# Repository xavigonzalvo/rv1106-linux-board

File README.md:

# RV1106G3 Linux board (Rev A)

An 80 × 80 mm Linux board around the Rockchip RV1106G3 (Cortex-A7, 256 MB DDR3L in package, 1 TOPS NPU), with
SPI NAND, microSD, 100 Mb Ethernet, USB-C (power + OTG), USB-A host and a 2×20 header.
Board #1 boots Linux, is on the network, runs YOLOv5 on the NPU (2026-11-20) and a 135M-parameter chat model on
the CPU (2026-11-21).

First bring-up (2026-11-20, details in `design/LOG.md` and `software/BOARD-QUICKSTART.md`): the blank board
appeared on the Mac as a Rockchip device in recovery mode, then booted Linux from its own flash and got on the
network.

| Recovery mode over USB-C | Linux on Ethernet |
|---|---|
|  |  |

| Folder | What |
|---|---|
| `PLAN.md` | the project plan and phases |
| `design/` | requirements, decisions (`decisions.md`), schematic, PCB (`pcb/`, fab files in `pcb/fab/`), bring-up procedure and log (`bringup.md`, `LOG.md`), datasheets and references (`refs/`) |
| `software/` | board support for the Luckfox SDK, flashing tools, Docker cross-compiler, examples |
| `software/BOARD-QUICKSTART.md` | **start here** to flash and use a board |
| `software/examples/ai-detect/` | object detection on the NPU with a web UI |
| `software/examples/tiny-llm/` | SmolLM2-135M-Instruct chat on the CPU (`chat` in the board shell) |
| `dashboard/` | project status page |
| `case/` | 3D-printable enclosure (OpenSCAD source + STLs, with and without the V-cut rails) |
| `release/rev-a/` | **ordering bundle**: JLCPCB upload zip, BOM, CPL, order notes, case STLs, device trees; rebuilt by `release/make_release.sh` |

## Not in this repo (fetch again when needed)

* `thirdparty/luckfox-image/` — Luckfox Pico Pro Max SPI NAND image 250607, from Luckfox's Google Drive (link in
  `software/BOARD-QUICKSTART.md` §3).
* `thirdparty/luckfox-toolchain/` — `software/docker/build.sh fetch-toolchain`.
* `software/tools/rkdeveloptool/` — github.com/rockchip-linux/rkdeveloptool commit 304f073, build steps in the quickstart §2.
* `thirdparty/luckfox_pico_rknn_example`, `rknn_model_zoo`, `stb` — reference sources only; what the detector needs is
  copied into `software/examples/ai-detect/detector/3rdparty/`.
* `thirdparty/smollm2-135m-instruct/` — the chat model from huggingface.co/HuggingFaceTB/SmolLM2-135M-Instruct and
  its int8 conversion; `software/examples/tiny-llm/deploy.sh` fetches and converts it.
* `thirdparty/llama2.c/` — github.com/karpathy/llama2.c commit 350e04f, the source `tiny-llm/llm.c` started from
  (reference only).
* `design/.venv/` — Python environment for the design tools.
* Intermediate PCB routing trials (`design/pcb/trial`, `l5`, `l5f`) and build outputs.

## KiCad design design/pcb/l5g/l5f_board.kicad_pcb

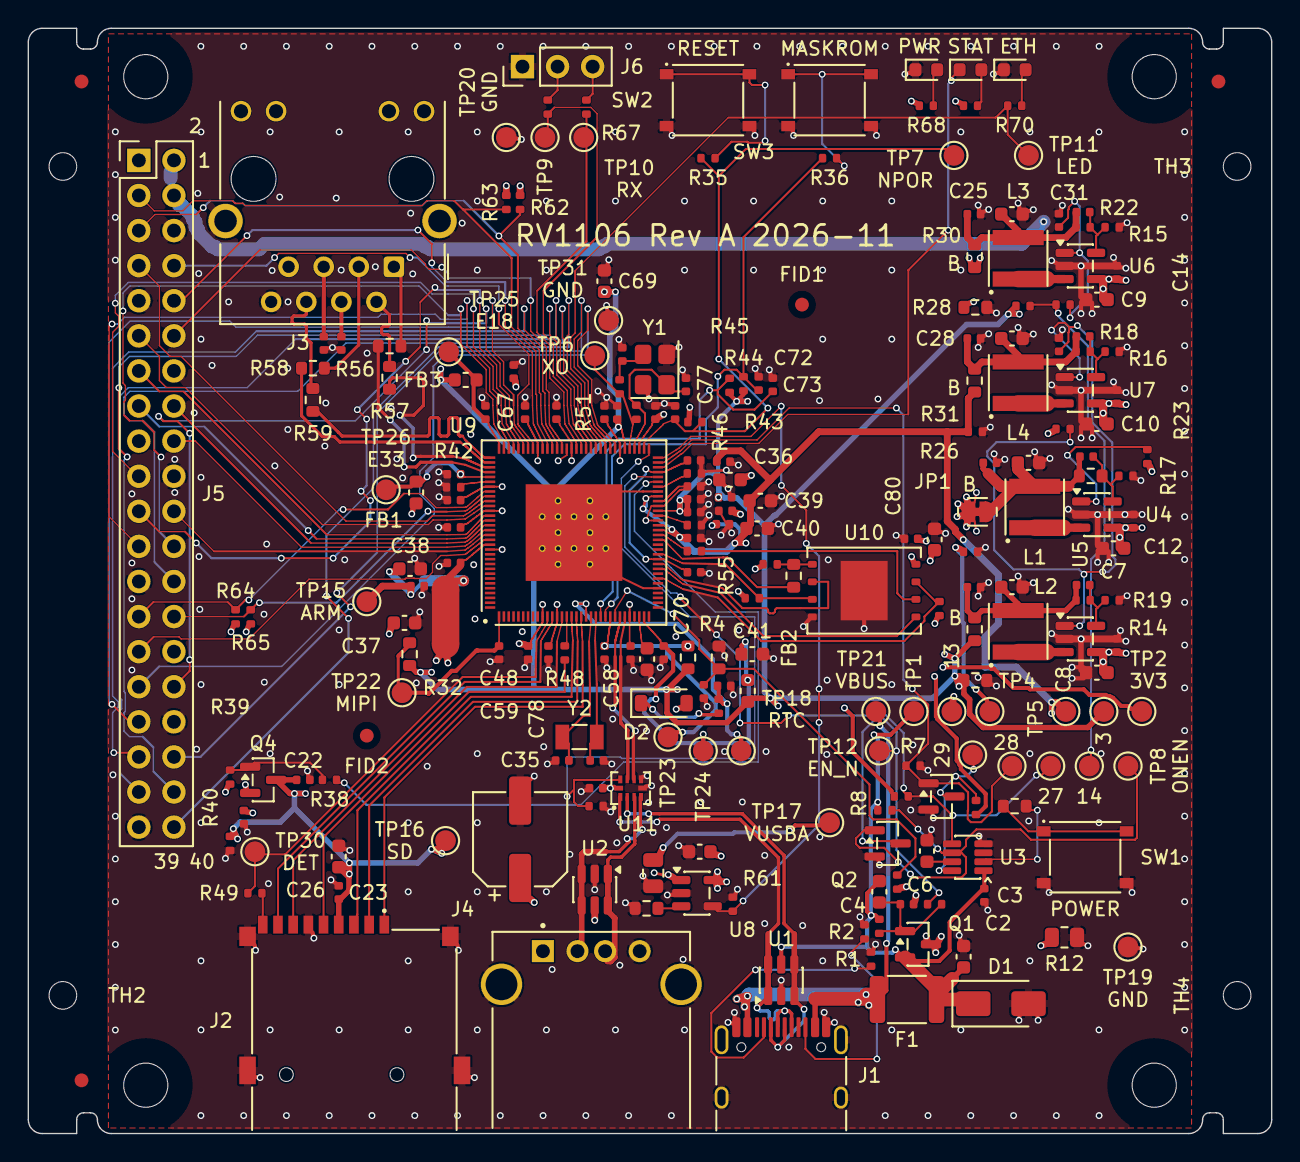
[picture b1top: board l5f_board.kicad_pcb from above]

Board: 4 copper layers, 90.0 x 80.0 mm, 239 parts (0 on the bottom side), 135 nets.

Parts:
C1, C3, C12, C13, C14, C15, C16, C17, C18, C19, C20, C21, C22, C23, C48, C49, C50, C51, C52, C53, C54, C55, C56, C57, C58, C59, C60, C61, C62, C63, C64, C65, C66, C67, C68, C71, C74, C81, C84: 100nF 16V X7R; C_0402_1005Metric
C2, C6: 2.2uF 16V X5R; C_0603_1608Metric
C4: 470nF 25V X7R; C_0603_1608Metric
C5, C82, C83: 10nF 50V X7R; C_0402_1005Metric
C7, C8, C9, C10, C11: 10uF 25V X5R; C_0603_1608Metric
C24, C27, C28: 22uF 6.3V X5R; C_0603_1608Metric
C25, C26, C36, C37, C38, C39, C40, C41, C80: 10uF 10V X5R; C_0603_1608Metric
C29, C30, C31, C32: 6.8pF 50V C0G; C_0402_1005Metric
C33: 150nF 16V X7R; C_0402_1005Metric
C34: 22uF 25V X5R; C_0805_2012Metric
C35: 120uF 10V polymer; CP_Elec_6.3x5.9
C42, C43, C44, C45, C46, C47, C75: 1uF 25V X5R; C_0402_1005Metric
C69, C70: 4.7uF 16V X5R; C_0603_1608Metric
C72, C73: 1nF 50V X7R; C_0402_1005Metric
C76, C77, C78, C79: 18pF 50V C0G; C_0402_1005Metric
D1: SMAJ5.0A; D_SMA
D2: B5819W SL; D_SOD-123
F1: BSMD1812-300-16V; Fuse_1812_4532Metric
FB1, FB2, FB3: BLM18PG121SN1D; L_0603_1608Metric
FID1, FID2: Fiducial; Fiducial_1mm_Mask2mm
GFID1, GFID2, GFID3: Fiducial; Fiducial_1mm_Mask2mm
H1, H2, H3, H4: M3 NPTH; MountingHole_3.2mm_M3
J1: TYPE-C-31-M-12; USB_C_Receptacle_HRO_TYPE-C-31-M-12
J2: TF-01A; microSD_TF-01A
J3: HR911105A; RJ45_Hanrun_HR911105A_Horizontal
J4: AF 90 WJDG; USB_A_AF90_WJDG_RightAngle_THT
J5: B-2100S40P-B110; PinHeader_2x20_P2.54mm_Vertical
J6: 1x3P 2.54mm; PinHeader_1x03_P2.54mm_Vertical
JP1: JP_MEAS_0V9; SolderJumper-2_P1.3mm_Bridged_RoundedPad1.0x1.5mm
L1, L2, L3, L4: FHD4020S-2R2MT; L_FHD4020S_4.0x4.0mm
LED1, LED2, LED3: KT-0603R red; LED_0603_1608Metric
NT1: NT_ARM; NetTie-2_SMD_Pad2.0mm
Q1: AO3401A; SOT-23
Q2: 2N7002; SOT-23
Q3: AO3400A; SOT-23
Q4: SI2301CDS-T1-GE3; SOT-23
R1, R2: 5.1k 1%; R_0402_1005Metric
R3, R23, R38, R40, R44, R45, R52, R53, R54, R60, R61: 10k 1%; R_0402_1005Metric
R4: 18k 1%; R_0603_1608Metric
R5, R6, R7, R8, R13, R14, R15, R16, R39, R46: 100k 1%; R_0402_1005Metric
R9: 47k 1%; R_0402_1005Metric
R10, R64, R65: 4.7k 1%; R_0402_1005Metric
R11, R29, R30, R31, R55, R56, R57, R58, R59: 0R 0603; R_0603_1608Metric
R12: 470R 1% 0805; R_0805_2012Metric
R17: 49.9k 1%; R_0603_1608Metric
R18: 127k 1%; R_0402_1005Metric
R19, R20, R21: 200k 1%; R_0402_1005Metric
R22: 442k 1%; R_0402_1005Metric
R24, R25, R26, R43, R66, R67, R68, R69, R70: 1k 1%; R_0402_1005Metric
R27, R28: 680R 1%; R_0603_1608Metric
R32, R33: 1R 1%; R_0603_1608Metric
R34, R35, R36, R49: 100R 1%; R_0402_1005Metric
R37: 6.8k 1%; R_0603_1608Metric
R41: 240R 1%; R_0402_1005Metric
R42: 6.04k 1%; R_0402_1005Metric
R47, R48, R50: 22R 1%; R_0402_1005Metric
R51: 1M 1%; R_0402_1005Metric
R62, R63: 2.2k 1%; R_0402_1005Metric
SW1, SW2, SW3: TS-1187A-B-A-B; SW_TS-1187A_5.1x5.1mm
TH1, TH2, TH3, TH4: Tooling 2.0 NPTH; MountingHole_2mm
TP1: TP_VBUS_5V; TestPoint_Pad_D1.5mm
TP2: TP_VCC_3V3; TestPoint_Pad_D1.5mm
TP3: TP_VCC_1V8; TestPoint_Pad_D1.5mm
TP4: TP_VDD_0V9; TestPoint_Pad_D1.5mm
TP5: TP_VCC_DDR; TestPoint_Pad_D1.5mm
TP6: TP_OSC_XOUT; TestPoint_Pad_D1.5mm
TP7: TP_NPOR; TestPoint_Pad_D1.5mm
TP8: TP_ONOFF_EN; TestPoint_Pad_D1.5mm
TP9: TP_UART2_TX; TestPoint_Pad_D1.5mm
TP10: TP_UART2_RX; TestPoint_Pad_D1.5mm
TP11: TP_LED_ETH; TestPoint_Pad_D1.5mm
TP12: TP_EN_N; TestPoint_Pad_D1.5mm
TP13: TP_VCC5V0_SYS; TestPoint_Pad_D1.5mm
TP14: TP_PWR_EN; TestPoint_Pad_D1.5mm
TP15: TP_VDD_ARM; TestPoint_Pad_D1.5mm
TP16: TP_VCC3V3_SD; TestPoint_Pad_D1.5mm
TP17: TP_VBUS_USBA; TestPoint_Pad_D1.5mm
TP18: TP_VCC3V3_RTC; TestPoint_Pad_D1.5mm
TP19: TP_GND1; TestPoint_Pad_D1.5mm
TP20: TP_GND2; TestPoint_Pad_D1.5mm
TP21: TP_VBUS_IN; TestPoint_Pad_D1.5mm
TP22: TP_MIPI_CSI_AVDD_1V8; TestPoint_Pad_D1.5mm
TP23: TP_AVDD1V8_USB; TestPoint_Pad_D1.5mm
TP24: TP_VCC1V8_CODEC; TestPoint_Pad_D1.5mm
TP25: TP_ETH_AVDD1V8; TestPoint_Pad_D1.5mm
TP26: TP_FEPHY_AVDD3V3; TestPoint_Pad_D1.5mm
TP27: TP_PB_INT_N; TestPoint_Pad_D1.5mm
TP28: TP_PWR_KILL; TestPoint_Pad_D1.5mm
TP29: TP_PWR_KILL_N; TestPoint_Pad_D1.5mm
TP30: TP_SDMMC_DET; TestPoint_Pad_D1.5mm
TP31: TP_GND3; TestPoint_Pad_D1.5mm
U1, U2: USBLC6-2SC6; SOT-23-6
U3: LTC2954CTS8-1#TRPBF; TSOT-23-8
U4, U5, U6, U7: TLV62569DBVR; SOT-23-5
U8: SY6280AAC; SOT-23-5
U9: RV1106G3; RV1106_QFN-128-1EP_12.3x12.3mm_P0.35mm
U10: W25N01KVZEIR; WSON-8-1EP_8x6mm_P1.27mm_EP3.4x4.3mm
U11: TS3USB221ARSER; TI_RSE0010A_UQFN-10_1.5x2mm_P0.5mm
Y1: TAXM24M4RFBCCT2T; Crystal_SMD_3225-4Pin_3.2x2.5mm
Y2: Q13FC13500004; Crystal_SMD_3215-2Pin_3.2x1.5mm

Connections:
AVDD1V8_USB: C58.1, R33.2, TP23.1, U9.24
CC1: J1.A5, R1.1
CC2: J1.B5, R2.1
CODEC_VCM: C70.1, U9.30
DRAM_ZQ: R41.1, U9.52
EN_N: Q2.3, R9.1, TP12.1
ETH_AVDD1V8: C56.1, FB3.2, TP25.1, U9.96
ETH_EXTR: R42.1, U9.102
ETH_RCT: C83.1, J3.5
ETH_RXN: R59.1, U9.97
ETH_RXN_J: J3.6, R59.2
ETH_RXP: R58.1, U9.98
ETH_RXP_J: J3.3, R58.2
ETH_TCT: C82.1, J3.4
ETH_TXN: R57.1, U9.99
ETH_TXN_J: J3.2, R57.2
ETH_TXP: R56.1, U9.100
ETH_TXP_J: J3.1, R56.2
FEPHY_AVDD3V3: C66.1, FB1.2, TP26.1, U9.101
FSPI_CLK: R47.1, U9.48
FSPI_CLK_NAND: R47.2, U10.6
FSPI_CS0N: R55.1, U9.47
FSPI_CS0N_NAND: R54.2, R55.2, U10.1
FSPI_D0: U9.41, U10.5
FSPI_D1: U9.42, U10.2
FSPI_D2: R53.2, U9.44, U10.3
FSPI_D3: R52.2, U9.39, U10.7
GND: C1.2, C2.2, C3.2, C6.2, C7.2, C8.2, C9.2, C10.2, C11.2, C12.2, C13.2, C14.2, C15.2, C16.2, C17.2, C18.2, C19.2, C20.2, C21.2, C22.2, C23.2, C24.2, C25.2, C26.2, C27.2, C28.2, C33.2, C34.2, C35.2, C36.2, C37.2, C38.2, C39.2, C40.2, C41.2, C42.2, C43.2, C44.2, C45.2, C46.2, C47.2, C48.2, C49.2, C50.2, C51.2, C52.2, C53.2, C54.2, C55.2, C56.2, C57.2, C58.2, C59.2, C60.2, C61.2, C62.2, C63.2, C64.2, C65.2, C66.2, C67.2, C68.2, C69.2, C70.2, C71.2, C72.2, C73.2, C74.2, C75.2, C76.2, C77.2, C78.2, C79.2, C80.2, C81.2, C82.2, C83.2, C84.2, D1.2, J1.A1, J1.A12, J1.B1, J1.B12, J1.SH, J2.6, J2.SH, J3.8, J3.SH, J4.4, J4.SH, J5.6, J5.9, J5.14, J5.20, J5.25, J5.30, J5.34, J5.39, J6.1, LED1.1, LED3.1, Q2.2, Q3.2, R1.2, R2.2, R4.2, R7.2, R12.2, R13.2, R14.2, R15.2, R16.2, R25.2, R26.2, R27.2, R28.2, R37.2, R40.2, R41.2, R42.2, R46.2, R60.2, R61.2, SW1.3, SW1.4, SW2.3, SW2.4, SW3.3, SW3.4, TP19.1, TP20.1, TP31.1, U1.2, U2.2, U3.4, U4.2, U5.2, U6.2, U7.2, U8.2, U9.37, U9.57, U9.129, U10.4, U10.9, U11.5, U11.6, Y1.2, Y1.4
GPIO0_A0_PD: R46.1, U9.58
HDR_GPIO1_A0: J5.31, U9.72
HDR_GPIO1_A1: J5.36, U9.73
HDR_GPIO1_A3: J5.40, U9.75
HDR_GPIO1_A4: J5.26, U9.76
HDR_GPIO1_B0: J5.37, U9.77
HDR_GPIO1_B1: J5.38, U9.78
HDR_GPIO2_A0: J5.13, U9.109
HDR_GPIO2_A1: J5.15, U9.110
HDR_GPIO2_A2: J5.16, U9.111
HDR_GPIO2_A3: J5.18, U9.112
HDR_GPIO2_A4: J5.22, U9.113
HDR_GPIO2_A5: J5.29, U9.114
HDR_GPIO2_A6: J5.11, U9.107
HDR_GPIO2_A7: J5.7, U9.106
HDR_I2C1_SCL: J5.28, R65.2, U9.105
HDR_I2C1_SDA: J5.27, R64.2, U9.104
HDR_I2C3_SCL: J5.5, R62.2, U9.85
HDR_I2C3_SDA: J5.3, R63.2, U9.86
HDR_PWM8: J5.32, U9.91
HDR_PWM9: J5.33, U9.90
HDR_PWM10: J5.12, U9.83
HDR_PWM11: J5.35, U9.84
HDR_SPI0_CS0: J5.24, U9.95
HDR_SPI0_MISO: J5.21, U9.92
HDR_SPI0_MOSI: J5.19, U9.93
HDR_SPI0_SCLK: J5.23, U9.94
HDR_UART3_RX: J5.10, U9.87
HDR_UART3_TX: J5.8, U9.89
LED_ETH: R70.1, TP11.1, U9.74
LED_ETH_A: LED3.2, R70.2
LED_PWR_A: LED1.2, R68.2
LED_STATUS: LED2.1, U9.62
LED_STAT_A: LED2.2, R69.2
MIPI_CSI_AVDD_1V8: C59.1, R32.2, TP22.1, U9.1
NPOR: C71.1, R35.1, R43.2, TP7.1, U9.66
NPOR_KEY: R35.2, SW2.1, SW2.2
ONOFF_EN: Q2.1, R8.2, TP8.1, U3.6
ONOFF_PDT: C6.1, U3.7
OSC_XIN: C77.1, R51.2, U9.68, Y1.1
OSC_XOUT: R50.1, R51.1, TP6.1, U9.69
OSC_XOUT_X: C76.1, R50.2, Y1.3
PB_IN: R11.2, U3.2
PB_INT_N: R10.2, TP27.1, U3.5, U9.60
PWR_BTN_N: R11.1, SW1.1, SW1.2
PWR_EN: R21.1, R24.2, TP14.1
PWR_KILL: Q3.1, R7.1, TP28.1, U9.63
PWR_KILL_N: Q3.3, R6.2, TP29.1, U3.8
QPWR_G: C4.1, C5.1, Q1.1, R5.1, R9.2
RECOVERY: C72.1, R36.1, R44.2, U9.23
RECOVERY_KEY: R36.2, SW3.1, SW3.2
RTC_XIN: C79.1, U9.21, Y2.1
RTC_XOUT: C78.1, U9.20, Y2.2
SARADC_IN1: C73.1, R45.2, U9.22
SDMMC_CLK: R48.1, U9.15
SDMMC_CLK_SD: J2.5, R48.2
SDMMC_CMD: J2.3, U9.16
SDMMC_D0: J2.7, U9.14
SDMMC_D1: J2.8, U9.12
SDMMC_D2: J2.1, U9.18
SDMMC_D3: J2.2, U9.17
SDMMC_DET: R49.1, TP30.1, U9.11
SDMMC_PWREN: R38.2, U9.59
SD_CD_SW: J2.9, R49.2
SD_PWR_G: Q4.1, R38.1, R39.2
U4_EN: R23.2, U4.1
U4_FB: C29.2, R13.1, R17.2, U4.5
U4_SW: L1.1, U4.3
U5_FB: C30.2, R14.1, R19.2, U5.5
U5_SW: L2.1, U5.3
U6_EN: C33.1, R21.2, U6.1
U6_FB: C31.2, R15.1, R22.2, U6.5
U6_SW: L3.1, U6.3
U7_FB: C32.2, R16.1, R18.2, U7.5
U7_SW: L4.1, U7.3
UART2_RX: R67.2, TP10.1, U9.80
UART2_RX_HDR: J6.3, R67.1
UART2_TX: R66.1, TP9.1, U9.79
UART2_TX_HDR: J6.2, R66.2
USBA_DM: J4.2, U2.3, U2.4, U11.4
USBA_DP: J4.3, U2.1, U2.6, U11.3
USBA_ISET: R37.1, U8.3
USBA_VBUS_EN: R61.1, U8.4, U9.64
USBC_DM: J1.A7, J1.B7, U1.3, U1.4, U11.2
USBC_DP: J1.A6, J1.B6, U1.1, U1.6, U11.1
USB_DET_IN: C1.1, R3.2, R4.1, U9.25
USB_DM: U9.26, U11.7
USB_DP: U9.27, U11.8
USB_SEL: R60.1, U9.65, U11.9
VBUS_5V: C2.1, C3.1, C4.2, D1.1, F1.2, Q1.2, R5.2, R8.1, TP1.1, U1.5, U3.1
VBUS_IN: F1.1, J1.A4, J1.A9, J1.B4, J1.B9, TP21.1
VBUS_USBA: C34.1, C35.1, J4.1, TP17.1, U2.5, U8.1
VCC1V8_CODEC: C41.1, C57.1, FB2.2, TP24.1, U9.31
VCC3V3_RTC: C75.1, R34.2, TP18.1, U9.19
VCC3V3_RTC_IN: D2.1, R34.1
VCC3V3_SD: C22.1, C23.1, C26.1, J2.4, Q4.3, R40.1, TP16.1
VCC5V0_SYS: C5.2, C7.1, C8.1, C9.1, C10.1, C11.1, C12.1, C13.1, C14.1, C15.1, J5.2, J5.4, Q1.3, R3.1, R12.1, R20.1, R23.1, TP13.1, U4.4, U5.4, U6.4, U7.4, U8.5
VCC_1V8: C47.1, C54.1, C55.1, C60.1, C69.1, FB2.1, FB3.1, R24.1, R27.1, R29.2, R32.1, R33.1, R44.1, R45.1, TP3.1, U9.53, U9.70
VCC_1V8_BUCK: C17.1, C27.1, C30.1, L2.2, R19.1, R29.1
VCC_3V3: C21.1, C61.1, C62.1, C63.1, C64.1, C65.1, C67.1, C68.1, C80.1, C81.1, C84.1, D2.2, FB1.1, J5.1, J5.17, Q4.2, R6.1, R10.1, R28.1, R30.2, R39.1, R43.1, R52.1, R53.1, R54.1, R62.1, R63.1, R64.1, R65.1, R68.1, R69.1, TP2.1, U9.13, U9.28, U9.43, U9.61, U9.81, U9.88, U9.108, U10.8, U11.10
VCC_3V3_BUCK: C18.1, C25.1, C31.1, L3.2, R22.1, R30.1
VCC_DDR: C39.1, C40.1, C45.1, C46.1, C53.1, R26.1, R31.2, TP5.1, U9.49, U9.50, U9.56
VCC_DDR_1V8_EN: C20.1, R20.2, U5.1, U7.1
VCC_DDR_BUCK: C19.1, C28.1, C32.1, L4.2, R18.1, R31.1
VDD_0V9: C36.1, C37.1, C42.1, C43.1, C48.1, C49.1, C50.1, C51.1, C74.1, JP1.2, NT1.1, R25.1, TP4.1, U9.10, U9.51, U9.54, U9.55, U9.67, U9.71, U9.82, U9.103, U9.116
VDD_0V9_BUCK: C16.1, C24.1, C29.1, JP1.1, L1.2, R17.1
VDD_ARM: C38.1, C44.1, C52.1, NT1.2, TP15.1, U9.115

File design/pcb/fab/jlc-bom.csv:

Comment,Designator,Footprint,LCSC Part #
TYPE-C-31-M-12,J1,USB_C_Receptacle_HRO_TYPE-C-31-M-12,C165948
5.1k 1%,"R1,R2",R_0402_1005Metric,C25905
10k 1%,"R3,R23,R38,R40,R44,R45,R52,R53,R54,R60,R61",R_0402_1005Metric,C25744
18k 1%,R4,R_0603_1608Metric,C25810
100nF 16V X7R,"C1,C3,C12,C13,C14,C15,C16,C17,C18,C19,C20,C21,C22,C23,C48,C49,C50,C51,C52,C53,C54,C55,C56,C57,C58,C59,C60,C61,C62,C63,C64,C65,C66,C67,C68,C71,C74,C81,C84",C_0402_1005Metric,C1525
BSMD1812-300-16V,F1,Fuse_1812_4532Metric,C883162
SMAJ5.0A,D1,D_SMA,C113952
USBLC6-2SC6,"U1,U2",SOT-23-6,C7519
2.2uF 16V X5R,"C2,C6",C_0603_1608Metric,C23630
LTC2954CTS8-1#TRPBF,U3,TSOT-23-8,C683782
AO3401A,Q1,SOT-23,C15127
2N7002,Q2,SOT-23,C8545
AO3400A,Q3,SOT-23,C20917
100k 1%,"R5,R6,R7,R8,R13,R14,R15,R16,R39,R46",R_0402_1005Metric,C25741
47k 1%,R9,R_0402_1005Metric,C25792
4.7k 1%,"R10,R64,R65",R_0402_1005Metric,C25900
0R 0603,"R11,R29,R30,R31,R55,R56,R57,R58,R59",R_0603_1608Metric,C21189
470nF 25V X7R,C4,C_0603_1608Metric,C1623
10nF 50V X7R,"C5,C82,C83",C_0402_1005Metric,C15195
470R 1% 0805,R12,R_0805_2012Metric,C17710
TS-1187A-B-A-B,"SW1,SW2,SW3",SW_TS-1187A_5.1x5.1mm,C318884
TLV62569DBVR,"U4,U5,U6,U7",SOT-23-5,C141836
FHD4020S-2R2MT,"L1,L2,L3,L4",L_FHD4020S_4.0x4.0mm,C602029
10uF 25V X5R,"C7,C8,C9,C10,C11",C_0603_1608Metric,C96446
22uF 6.3V X5R,"C24,C27,C28",C_0603_1608Metric,C59461
10uF 10V X5R,"C25,C26,C36,C37,C38,C39,C40,C41,C80",C_0603_1608Metric,C19702
6.8pF 50V C0G,"C29,C30,C31,C32",C_0402_1005Metric,C1576
49.9k 1%,R17,R_0603_1608Metric,C23184
127k 1%,R18,R_0402_1005Metric,C25751
200k 1%,"R19,R20,R21",R_0402_1005Metric,C25764
442k 1%,R22,R_0402_1005Metric,C5101
1k 1%,"R24,R25,R26,R43,R66,R67,R68,R69,R70",R_0402_1005Metric,C11702
680R 1%,"R27,R28",R_0603_1608Metric,C23228
150nF 16V X7R,C33,C_0402_1005Metric,C162182
1R 1%,"R32,R33",R_0603_1608Metric,C22936
BLM18PG121SN1D,"FB1,FB2,FB3",L_0603_1608Metric,C14709
B5819W SL,D2,D_SOD-123,C8598
100R 1%,"R34,R35,R36,R49",R_0402_1005Metric,C25076
SY6280AAC,U8,SOT-23-5,C55136
6.8k 1%,R37,R_0603_1608Metric,C23212
22uF 25V X5R,C34,C_0805_2012Metric,C45783
120uF 10V polymer,C35,CP_Elec_6.3x5.9,C250087
SI2301CDS-T1-GE3,Q4,SOT-23,C10487
RV1106G3,U9,RV1106_QFN-128-1EP_12.3x12.3mm_P0.35mm_EPboardvias,C5328706
1uF 25V X5R,"C42,C43,C44,C45,C46,C47,C75",C_0402_1005Metric,C52923
4.7uF 16V X5R,"C69,C70",C_0603_1608Metric,C19666
240R 1%,R41,R_0402_1005Metric,C114755
6.04k 1%,R42,R_0402_1005Metric,C97819
1nF 50V X7R,"C72,C73",C_0402_1005Metric,C1523
22R 1%,"R47,R48,R50",R_0402_1005Metric,C25092
TAXM24M4RFBCCT2T,Y1,Crystal_SMD_3225-4Pin_3.2x2.5mm,C164058
Q13FC13500004,Y2,Crystal_SMD_3215-2Pin_3.2x1.5mm,C32346
18pF 50V C0G,"C76,C77,C78,C79",C_0402_1005Metric,C1549
1M 1%,R51,R_0402_1005Metric,C26083
W25N01KVZEIR,U10,WSON-8-1EP_8x6mm_P1.27mm_EP3.4x4.3mm,C22472329
TF-01A,J2,microSD_TF-01A,C91145
HR911105A,J3,RJ45_Hanrun_HR911105A_Horizontal,C12074
TS3USB221ARSER,U11,TI_RSE0010A_UQFN-10_1.5x2mm_P0.5mm,C128396
AF 90 WJDG,J4,USB_A_AF90_WJDG_RightAngle_THT,C456018
B-2100S40P-B110,J5,PinHeader_2x20_P2.54mm_Vertical,C124383
2.2k 1%,"R62,R63",R_0402_1005Metric,C25879
1x3P 2.54mm,J6,PinHeader_1x03_P2.54mm_Vertical,C49257
KT-0603R red,"LED1,LED2,LED3",LED_0603_1608Metric,C2286

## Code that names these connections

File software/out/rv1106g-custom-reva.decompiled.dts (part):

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			gpio-ranges = <0x4c 0x00 0x00 0x20>;
			interrupt-controller;
			#interrupt-cells = <0x02>;
			gpio-line-names = "", "SDMMC_PWREN", "PB_INT_N", "LED_STATUS", "PWR_KILL", "USBA_VBUS_EN", "USB_SEL", "", "", "", "", "", "", "", "", "", "", "", "", "", "", "", "", "", "", "", "", "", "", "", "", "";
			phandle = <0x58>;

			sdmmc-pwren-hog {
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			gpio-ranges = <0x4c 0x00 0x40 0x20>;
			interrupt-controller;
			#interrupt-cells = <0x02>;
			gpio-line-names = "HDR_GPIO2_A0", "HDR_GPIO2_A1", "HDR_GPIO2_A2", "HDR_GPIO2_A3", "HDR_GPIO2_A4", "HDR_GPIO2_A5", "HDR_GPIO2_A6", "HDR_GPIO2_A7", "HDR_I2C1_SCL", "HDR_I2C1_SDA", "", "", "", "", "", "", "", "", "", "", "", "", "", "", "", "", "", "", "", "", "", "";
			phandle = <0xb2>;
		};

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			gpio-ranges = <0x4c 0x00 0x60 0x20>;
			interrupt-controller;
			#interrupt-cells = <0x02>;
			gpio-line-names = "", "SDMMC_DET", "SDMMC_D1", "SDMMC_D0", "SDMMC_CLK", "SDMMC_CMD", "SDMMC_D3", "SDMMC_D2", "", "", "", "", "", "", "", "", "", "", "", "", "", "", "", "", "", "", "", "", "", "", "", "";
			phandle = <0xb3>;
		};

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			gpio-ranges = <0x4c 0x00 0x80 0x20>;
			interrupt-controller;
			#interrupt-cells = <0x02>;
			gpio-line-names = "", "", "FSPI_D2", "FSPI_D1", "FSPI_D0", "", "FSPI_D3", "", "FSPI_CS0N", "FSPI_CLK", "", "", "", "", "", "", "RECOVERY", "SARADC_IN1", "", "", "", "", "", "", "", "", "", "", "", "", "", "";
			phandle = <0xb4>;
		};

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
		board-gpio {

			pb_int_n_pin: pb-int-n-pin {
				rockchip,pins = <0x00 0x02 0x00 0x4d>;
				phandle = <0x57>;
			};

			pwr_kill_pin: pwr-kill-pin {
				rockchip,pins = <0x00 0x04 0x00 0x55>;
				phandle = <0x59>;
			};

			led_status_pin: led-status-pin {
				rockchip,pins = <0x00 0x03 0x00 0x4d>;
				phandle = <0x5a>;
			};

			led_eth_pin: led-eth-pin {
				rockchip,pins = <0x01 0x02 0x00 0x4d>;
				phandle = <0x5b>;
			};
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		vicap_d15 = "/pinctrl/vicap/vicap-d15";
		vicap_clkout_m0 = "/pinctrl/vicap/vicap-clkout-m0";
		vicap_clkout_m1 = "/pinctrl/vicap/vicap-clkout-m1";
		pb_int_n_pin = "/pinctrl/board-gpio/pb-int-n-pin";
		pwr_kill_pin = "/pinctrl/board-gpio/pwr-kill-pin";
		led_status_pin = "/pinctrl/board-gpio/led-status-pin";
		led_eth_pin = "/pinctrl/board-gpio/led-eth-pin";
		rockchip_amp = "/rockchip-amp";
		vcc_1v8 = "/vcc-1v8";
		vcc_3v3 = "/vcc-3v3";
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
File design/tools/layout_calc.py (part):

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    ("Z-NAND", 49.5, 28.0, 61.5, 44.0, "zone", "U10 SPI NAND + C80/C81 + R52-R55"),
    ("Z-USB", 27.0, 50.0, 45.5, 64.5, "zone",
     "U11 USB mux + C84 + R60; U2 USB-A ESD and C35 at the south end next to J4; U8 SY6280 + C11/C34/R37/R61 in the "
     "south-east corner (VBUS_USBA to J4 pin 1 <= 15 mm)"),
    ("Z-USBA-PWR", 45.5, 50.0, 55.0, 71.0, "zone",
     "U1 USB-C ESD at the south end, <= 3 mm from J1 A6/A7/B6/B7; TP17; L3 below carries the VCC5V0_SYS feed to U8"),
    ("Z-PWRIN", 55.0, 48.0, 77.0, 72.5, "zone",
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    p1 = (ux - 1.1375, uy - 0.95)  # SOT-23-5 pad 1 at (-1.1375, -0.95), rotation 0 (cached KiCad footprint)
    for jx, jy in J4_PIN1_CANDIDATES:
        d = octi(p1, (jx, jy)) * DETOUR
        rows.append(dict(item="VBUS_USBA U8 -> J4 pin 1", path=f"U8 pin 1 ({p1[0]:.2f}, {p1[1]:.2f}) -> J4 pin 1 candidate "
                         f"({jx}, {jy})", length_mm=round(d, 1), limit_mm=VBUS_USBA_MAX, r_mohm="", current_a="",
                         value=round(d, 1), unit="mm", note=f"octilinear x {DETOUR} detour (as lengths.csv); D-81 limit"))
    return rows
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    "ETH_CT": (0.30, 0.15, "", "C82/C83 <= 3 mm from J3 pins 4/5", "", "layout.md §4.2"),
}
XTAL_LEN = {  # one XTAL length budget (round 3): layout.md §4.1/§4.3, netclasses.csv and board.kicad_dru say the same
    "OSC_XIN": (5.0, "OSC_XIN <= 5 mm (pin 68 - Y1 pin 1 - C77 - R51)"),
    "OSC_XOUT_X": (5.0, "OSC_XOUT_X <= 5 mm (R50 - Y1 pin 3 - C76)"),
    "OSC_XOUT": (8.0, "OSC_XOUT <= 8 mm total: pin 69 -> R50 <= 2 mm, R51 branch <= 2 mm, TP6 stub <= 3 mm"),
    "RTC_XIN": (6.0, "RTC_XIN <= 6 mm (pin 21 - Y2 - C79)"),
    "RTC_XOUT": (6.0, "RTC_XOUT <= 6 mm (pin 20 - Y2 - C78)"),
}
for cls, nets, i_a, basis, w_out, w_in in POWER_CLASSES:
    if cls != "SW_NODE":
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    u10 = zone_pt("Z-NAND", "centre")
    u11 = U11_XY  # U11 under SoC pins 26/27, north part of Z-USB (stated point, unchanged since round 2)
    paths = []
    for n, (pin, j3pad) in {"ETH_TXP": (100, "1"), "ETH_TXN": (99, "2"), "ETH_RXP": (98, "3"), "ETH_RXN": (97, "6")}.items():
        paths.append(("ETH_DIFF", n + " + " + n + "_J", pin, [("J3." + j3pad, lib_pad("J3", j3pad))]))
    paths.append(("USB_DIFF", "USB_DP/DM -> U11 -> USBC_DP/DM -> J1 A6/A7", 27, [("U11", u11), ("J1.A6", lib_pad("J1", "A6"))]))
    paths.append(("USB_DIFF", "USB_DP/DM -> U11 -> USBA_DP/DM -> J4 2/3", 27, [("U11", u11), ("J4.2/3", j4)]))
    for n, pin in {"SDMMC_CLK + SDMMC_CLK_SD": 15, "SDMMC_CMD": 16, "SDMMC_D0": 14, "SDMMC_D1": 12, "SDMMC_D2": 18,
                   "SDMMC_D3": 17}.items():
        paths.append(("SDMMC", n, pin, [("J2", j2)]))
    for n, pin in {"FSPI_CLK + FSPI_CLK_NAND": 48, "FSPI_CS0N + FSPI_CS0N_NAND": 47, "FSPI_D0": 41, "FSPI_D1": 42,
                   "FSPI_D2": 44, "FSPI_D3": 39}.items():
        paths.append(("FSPI", n, pin, [("U10", u10)]))
    out = []
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SPECIAL_RULE = {
    "U9": f"centre {SOC_C}, rotation +90 deg: pin 1 at the SW corner, pins 1-32 on the south side W->E, 33-64 east "
          "S->N, 65-96 north E->W, 97-128 west N->S; 2 local fiducials diagonal (layout.md §6)",
    "Y1": "ring 1: crystal body <= 3 mm from SoC pins 68/69; OSC_XIN, OSC_XOUT_X <= 5 mm each; OSC_XOUT <= 8 mm total "
          "incl. the TP6 stub; GND guard (layout.md §4.3)",
    "Y2": "ring 1/2: crystal body <= 4 mm from SoC pins 20/21; RTC_XIN, RTC_XOUT <= 6 mm each; GND guard",
    "C76": "next to Y1 pin 3: <= 2 mm pad-to-pad, GND via at the pad", "C77": "next to Y1 pin 1: <= 2 mm pad-to-pad, GND via at the pad",
    "C78": "next to Y2: <= 2 mm pad-to-pad, GND via at the pad", "C79": "next to Y2: <= 2 mm pad-to-pad, GND via at the pad",
    "TP6": "test pad on OSC_XOUT (SoC pin 69 side of R50): <= 5 mm from SoC pin 69, stub <= 3 mm (testpoints.md §2 rule 3)",
    "TP31": "GND test pad within 3 mm of TP6 (scope ground for TP6, testpoints.md §2 rule 3)",
    "JP1": f"solder jumper U4 output -> VDD_0V9 L3 neck: centre {JP1_XY}, rotation 180 deg (pad 2 = VDD_0V9 west), "
           f">= 6 vias west of pad 2 (x 61.6-62.9) into the neck (layout.md §2.3, §3)",
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    "U6": "cell y 12-21 of Z-PMU (north); VIN/C_IN east, output west to R30", "U7": "cell y 21-30 of Z-PMU; output west to R31",
    "U5": "cell y 39-48 of Z-PMU (south); output west to R29",
    "U8": f"south-east corner of Z-USB, centre {U8_XY}, rotation 0 (pin 1 OUT north-west, pin 5 IN north-east); "
          f"VBUS_USBA path U8 pin 1 -> J4 pin 1 <= {VBUS_USBA_MAX:g} mm (layout.md §3, power_paths.csv)",
    "R37": "R_SET 6.8k (USBA_ISET, SENSE): <= 2 mm from U8 pin 3, south-west of U8, GND via at the pad",
    "TP17": "VBUS_USBA test pad: L1 stub to the VBUS_USBA pour or C34, <= 10 mm from U8 (testpoints.md §2)",
    "C34": "C_USBA_OUT 22 uF: <= 2 mm pad-to-pad from U8 pin 1, west of U8 in the Z-USB south-east corner, GND via at the pad",
    "NT1": "net-tie VDD_0V9 -> VDD_ARM at SoC pin 115, <= 8 mm, >= 0.6 mm copper (D-68)",
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    "U1": "south end of Z-USBA-PWR, within 3 mm of J1 A6/A7/B6/B7, flow-through",
    "U2": "south end of Z-USB, within 3 mm of J4 pins 2/3, flow-through",
    "C35": "120 uF polymer at J4 pin 1 (VBUS): <= 5 mm pad-to-pad, south end of Z-USB",
    "F1": "first part after J1 VBUS pins (west edge of Z-PWRIN, next to J1); VBUS_IN copper >= 1.0 mm",
    "D1": "TVS right after F1, GND via at the pad",
    "R42": "ETH_EXTR 6.04k <= 3 mm from SoC pin 102, GND via at the pad",
    "R41": "DRAM_ZQ 240R <= 3 mm from SoC pin 52, GND via at the pad",
    "C70": "CODEC_VCM 4.7u <= 3 mm from SoC pin 30 (reference node, ring 1)",
    "C6": "ONOFF_PDT cap <= 3 mm from U3 pin 7 (high-impedance timing node)",
    "R47": "22R within 2 mm of SoC pin 48 (source series termination)",
    "R48": "22R within 2 mm of SoC pin 15 (source series termination)",
    "R50": "22R within 2 mm of SoC pin 69", "R51": "1M across pins 68/69, within 2 mm of them",
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
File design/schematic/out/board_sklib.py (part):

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            Pin(num='17',name='SDMMC0_D3/UART5_TX_M0/JTAG_CPU_TMS_M0/JTAG_HPMCU_TMS_M1/GPIO3_A6_u',func=pin_types.PASSIVE),
            Pin(num='18',name='SDMMC0_D2/UART5_RX_M0/JTAG_CPU_TCK_M0/JTAG_HPMCU_TCK_M1/GPIO3_A7_u',func=pin_types.PASSIVE),
            Pin(num='19',name='RTC_AVDD3V3',func=pin_types.PWRIN),
            Pin(num='20',name='RTC_XOUT',func=pin_types.PASSIVE),
            Pin(num='21',name='RTC_XIN',func=pin_types.PASSIVE),
            Pin(num='22',name='SARADC_IN1/PWM1_M1/GPI4_C1_z',func=pin_types.PASSIVE),
            Pin(num='23',name='SARADC_IN0/GPI4_C0_z',func=pin_types.PASSIVE),
            Pin(num='24',name='SARADC_USB_AVDD1V8',func=pin_types.PWRIN),
            Pin(num='25',name='USB_VBUSDET',func=pin_types.PASSIVE),
            Pin(num='26',name='USB_DM',func=pin_types.PASSIVE),
            Pin(num='27',name='USB_DP',func=pin_types.PASSIVE),
            Pin(num='28',name='USB_AVDD3V3',func=pin_types.PWRIN),
            Pin(num='29',name='CODEC_LINEOUT',func=pin_types.PASSIVE),
            Pin(num='30',name='CODEC_VCM',func=pin_types.PASSIVE),
            Pin(num='31',name='CODEC_AVDD1V8',func=pin_types.PWRIN),
            Pin(num='32',name='CODEC_MICBIAS',func=pin_types.PASSIVE),
            Pin(num='33',name='CODEC_MIC0N',func=pin_types.PASSIVE),
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            Pin(num='36',name='CODEC_MIC1P',func=pin_types.PASSIVE),
            Pin(num='37',name='CODEC_AVSS',func=pin_types.PASSIVE),
            Pin(num='38',name='EMMC_D5/SPI1_CLK_M0/UART1_RX_M2/I2C2_SCL_M1/GPIO4_A7_u',func=pin_types.PASSIVE),
            Pin(num='39',name='EMMC_D3/FSPI_D3/GPIO4_A6_u',func=pin_types.PASSIVE),
            Pin(num='40',name='EMMC_D4/SPI1_CS0_M0/UART1_TX_M2/I2C2_SDA_M1/GPIO4_A5_u',func=pin_types.PASSIVE),
            Pin(num='41',name='EMMC_D0/FSPI_D0/GPIO4_A4_u',func=pin_types.PASSIVE),
            Pin(num='42',name='EMMC_D1/FSPI_D1/GPIO4_A3_u',func=pin_types.PASSIVE),
            Pin(num='43',name='GPIO3_VCC',func=pin_types.PWRIN),
            Pin(num='44',name='EMMC_D2/FSPI_D2/GPIO4_A2_u',func=pin_types.PASSIVE),
            Pin(num='45',name='EMMC_D6/SPI1_MOSI_M0/UART0_TX_M2/I2C0_SCL_M1/GPIO4_A1_u',func=pin_types.PASSIVE),
            Pin(num='46',name='EMMC_D7/SPI1_MISO_M0/UART0_RX_M2/I2C0_SDA_M1/GPIO4_A0_u',func=pin_types.PASSIVE),
            Pin(num='47',name='EMMC_CMD/FSPI_CS0/GPIO4_B0_u',func=pin_types.PASSIVE),
            Pin(num='48',name='EMMC_CLK/FSPI_CLK/GPIO4_B1_d',func=pin_types.PASSIVE),
            Pin(num='49',name='DDR_VDDQ_1',func=pin_types.PWRIN),
            Pin(num='50',name='DDR_VDDQ_2',func=pin_types.PWRIN),
            Pin(num='51',name='DVDD_2',func=pin_types.PWRIN),
            Pin(num='52',name='DRAM_ZQ',func=pin_types.PASSIVE),
            Pin(num='53',name='DDR_PLL_AVDD1V8',func=pin_types.PWRIN),
            Pin(num='54',name='DVDD_3',func=pin_types.PWRIN),
            Pin(num='55',name='DVDD_4',func=pin_types.PWRIN),
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            Pin(num='63',name='PMIC_PWR_CTRL_M0/PWM1_M0/GPIO0_A4_d',func=pin_types.PASSIVE),
            Pin(num='64',name='I2C1_SCL_M0/UART1_RTS_M0/PWM5_M0/GPIO0_A5_d',func=pin_types.PASSIVE),
            Pin(num='65',name='I2C1_SDA_M0/UART1_CTS_M0/PWM6_M0/GPIO0_A6_d',func=pin_types.PASSIVE),
            Pin(num='66',name='nPOR',func=pin_types.PASSIVE),
            Pin(num='67',name='PMU_DVDD0V9',func=pin_types.PWRIN),
            Pin(num='68',name='OSC_XIN',func=pin_types.PASSIVE),
            Pin(num='69',name='OSC_XOUT',func=pin_types.PASSIVE),
            Pin(num='70',name='OSC_AVDD1V8/PLL_AVDD1V8',func=pin_types.PWRIN),
            Pin(num='71',name='OSC_PLL_DVDD',func=pin_types.PWRIN),
            Pin(num='72',name='UART3_TX_M0/I2C2_SCL_M0/PWM7_IR_M0/GPIO1_A0_d',func=pin_types.PASSIVE),
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            Pin(num='93',name='VO_LCDC_D5/VI_CIF_D4_M1/PWM5_M2/I2C4_SCL_M1/SDMMC1_CLK_M1/SPI0_MOSI_M0/GPIO1_C2_d',func=pin_types.PASSIVE),
            Pin(num='94',name='VO_LCDC_D6/VI_CIF_D3_M1/PWM4_M2/SPI0_CLK_M0/SDMMC1_D0_M1/GPIO1_C1_d',func=pin_types.PASSIVE),
            Pin(num='95',name='VO_LCDC_D7/VI_CIF_D2_M1/PWM2_M2/SPI0_CS0_M0/SDMMC1_D1_M1/GPIO1_C0_d',func=pin_types.PASSIVE),
            Pin(num='96',name='OTP_AVDD1V8/ETH_AVDD1V8/TSADC_AVDD1V8',func=pin_types.PWRIN),
            Pin(num='97',name='ETH_PHY_RXN',func=pin_types.PASSIVE),
            Pin(num='98',name='ETH_PHY_RXP',func=pin_types.PASSIVE),
            Pin(num='99',name='ETH_PHY_TXN',func=pin_types.PASSIVE),
            Pin(num='100',name='ETH_PHY_TXP',func=pin_types.PASSIVE),
            Pin(num='101',name='ETH_AVDD3V3',func=pin_types.PWRIN),
            Pin(num='102',name='ETH_EXTR',func=pin_types.PASSIVE),
            Pin(num='103',name='DVDD_6',func=pin_types.PWRIN),
            Pin(num='104',name='UART0_TX_M1/I2C1_SDA_M1/VO_LCDC_D17/PWM6_M1/GPIO2_B1_d',func=pin_types.PASSIVE),
            Pin(num='105',name='UART0_RX_M1/I2C1_SCL_M1/VO_LCDC_D16/PWM5_M1/GPIO2_B0',func=pin_types.PASSIVE),
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            Pin(num='107',name='UART0_RTS_M1/I2S0_SDO2_SDI2/VO_LCDC_D14/PWM2_M1/I2C3_SCL_M0/FLASH_TRIG_OUT/GPIO2_A6_d',func=pin_types.PASSIVE),
            Pin(num='108',name='GPIO5_VCC',func=pin_types.PWRIN),
            Pin(num='109',name='SDMMC1_D1_M0/I2S0_SCLK/VO_LCDC_D8/UART1_CTS_M1/I2C4_SDA_M0/GPIO2_A0_d',func=pin_types.PASSIVE),
            Pin(num='110',name='SDMMC_D0/I2S0_LRCK/VO_LCDC_D9/UART1_RTS_M1/I2C4_SCL_M0/GPIO2_A1',func=pin_types.PASSIVE),
            Pin(num='111',name='SDMMC1_CLK_M0/I2S0_MCLK/VO_LCDC_D10/GPIO2_A2_d',func=pin_types.PASSIVE),
            Pin(num='112',name='SDMMC1_CMD_M0/I2S0_SDO3_SDI1/VO_LCDC_D11/GPIO2_A3_d',func=pin_types.PASSIVE),
            Pin(num='113',name='SDMMC1_D3_M0/I2S0_SDO0/VO_LCDC_D12/UART1_TX_M1/GPIO2_A4_d',func=pin_types.PASSIVE),
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
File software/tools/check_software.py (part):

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
def norm_fn(s):
    s = s.lower()
    s = re.sub(r"(cs\d)n", r"\1", s)  # pinctrl comments say cs0n / fspi_cs0n
    return s


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# ----------------------------------------------------------------------------- the checks
EXPECTED_GPIO = {
    # (consumer node path, property): (pinmap net, required flags)  flags: 0 active-high, 1 active-low
    ("/gpio-keys/power-key", "gpios"): ("PB_INT_N", 1),
    ("/gpio-poweroff", "gpios"): ("PWR_KILL", 0),
    ("/leds/led-status", "gpios"): ("LED_STATUS", 1),
    ("/leds/led-eth", "gpios"): ("LED_ETH", 0),
}

FORBIDDEN_ENABLED = ["i2c0", "i2c2", "i2c4", "uart0", "uart1", "uart4", "uart5", "pwm0", "pwm1", "pwm2", "pwm3",
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    po = T.find("/gpio-poweroff")
    ok = (gk is not None and gk.enabled() and gk.str("compatible") == "gpio-keys" and pk is not None
          and pk.u32("linux,code") == [116])
    check(ok, P + "S8", "gpio-keys power-key: linux,code = KEY_POWER (116) on PB_INT_N (pin 60, GPIO0_A2), active-low")
    pull_ok = False
    if po is not None:
        for ph in po.u32("pinctrl-0") or []:
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    row = by_gpio.get((0, 4))
    check(po is not None and po.enabled() and po.str("compatible") == "gpio-poweroff" and pull_ok
          and row["reset_pull"] == "pull-down", P + "S8",
          "gpio-poweroff on PWR_KILL (pin 63, GPIO0_A4) active-high, pinctrl GPIO + pull-down = pinmap reset pull (%s)" % row["reset_pull"])

    return host, gadget

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          "(inference; confirmed at bring-up by S15board)")
    gpo = open(os.path.join(proj, REL["ref_cfg"], "sysdrv/source/kernel/drivers/power/reset/gpio-poweroff.c")).read()
    check("flags = GPIOD_OUT_LOW;" in gpo and "gpiod_direction_output(reset_gpio, 1);" in gpo, "S8",
          "gpio-poweroff (5.10.160) holds PWR_KILL inactive from probe and drives it active in pm_power_off")
    # optional patch applies to the reference source
    w = os.path.join(tmp, "patchtest")
    os.makedirs(os.path.join(w, "drivers/power/reset"))
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    txt = open(script).read()
    unit = g0path.rsplit("@", 1)[1]
    check("GPIO0_DEV=%s.gpio" % unit in txt and "OFF_VBUS=5" in txt and "OFF_SEL=6" in txt
          and by_gpio_global[(0, 5)]["net"] == "USBA_VBUS_EN" and by_gpio_global[(0, 6)]["net"] == "USB_SEL",
          "S11", "board-usb targets gpio0 = %s.gpio, offsets 5 = USBA_VBUS_EN (pin 64), 6 = USB_SEL (pin 65)" % unit)
    results = {}
    for mode, drm in (("auto", "host"), ("auto", "peripheral"), ("off", "host")):
        root = os.path.join(tmp, "fake_%s_%s" % (mode, drm))
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    pins = {c: k for (k, f, c) in grp}
    tx, rx = pins.get("uart2_tx_m1"), pins.get("uart2_rx_m1")
    ok = (fiq.enabled() and fiq.u32("rockchip,serial-id") == [2] and fiq.u32("rockchip,baudrate") == [115200]
          and "console=ttyFIQ0" in ba and tx and rx and by_gpio[tx]["net"] == "UART2_TX" and by_gpio[rx]["net"] == "UART2_RX")
    check(ok, "S12", "console: fiq-debugger serial-id 2 @ 115200, console=ttyFIQ0; uart2m1 TX %s = pin %s, RX %s = pin %s"
          % (gpio_name(tx) if tx else "?", by_gpio[tx]["pin"] if tx else "?", gpio_name(rx) if rx else "?", by_gpio[rx]["pin"] if rx else "?"))

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    ("1416 MHz OPP kept", "\t/delete-node/ opp-1416000000;\n", ""),
    ("spi0 with cs1", "pinctrl-0 = <&spi0m0_pins &spi0m0_cs0>;", "pinctrl-0 = <&spi0m0_pins &spi0m0_cs0 &spi0m0_cs1>;"),
    ("restart-poweroff kept", "\t/delete-node/ restart-poweroff;\n", ""),
    ("wrong line name", '"HDR_GPIO2_A6", "HDR_GPIO2_A7"', '"HDR_GPIO2_A7", "HDR_GPIO2_A6"'),
    ("sdmmc non-removable", "\tdisable-wp;\n", "\tdisable-wp;\n\tnon-removable;\n"),
    ("uart0 enabled", "&uart3 {", "&uart0 {\n\tstatus = \"okay\";\n};\n\n&uart3 {"),
    ("LED_STATUS via pmic_sleep_m1", "<0 RK_PA3 RK_FUNC_GPIO &pcfg_pull_none>", "<0 RK_PA3 1 &pcfg_pull_none>"),
]


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
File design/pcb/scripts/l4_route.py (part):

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        yk = SD_Y0 + SD_PITCH * k
        ck = c0 + dc * k
        xt = ck - yk                       # where the horizontal turns south-west
        if pin is None:                    # SDMMC_DET: NW-most line of the bundle, leaves it towards TP30 / R49
            e = lane_end(net)
            pts = [e["back"], (xv, yk), (xt, yk), (13.6, ck - 13.6)]
            fixed(net, "F", pts)
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    if fixed_via("USB_DM", 37.30, 49.20) and fixed_via("USB_DM", 38.95, 50.85):
        fixed("USB_DM", "B", [(37.30, 49.20), (38.95, 50.85)], w=USBW)
        fixed("USB_DM", "F", [(38.95, 50.85), (38.804, 50.996), (38.804, 54.362)], w=USBW)
    # ---- south of U11 (pins W->E: USBC_DP, USBC_DM, USBA_DP, USBA_DM). USB-C dives right under U11 and crosses east
    # under the USB-A pair on L4 (D-108 a); USB-A leaves coupled (pitch 0.407) and USBA_DM swaps under USBA_DP.
    fixed("USBC_DP", "F", [(37.80, 55.638), (37.80, 57.45)], w=USBW)
    fixed("USBC_DM", "F", [(38.35, 55.638), (38.35, 56.85)], w=USBW)
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    fixed("USBA_DM", "F", [(36.80, an[-1][1]), (35.05 + 0.2, an[-1][1]), (35.05, an[-1][1] + 0.2), (35.05, 61.213)],
          w=W45)
    fixed("USBA_DP", "F", [(36.95, 61.213), (36.95, 63.487)], w=W45)
    # USBA_DP is the short line of the USB-A pair (its pin U2.1 is the near one at the split): it steps 0.5 mm east
    # under U2's south edge (>= 0.76 mm from the U2.5 VBUS_USBA via stub) and enters J4.3 from the south, which adds
    # the length the pad-to-pad skew needs without a meander between the U2.5 stub and the R37 / J4.4 GND copper
    fixed("USBA_DP", "F", [(36.95, 63.487), (36.95, 63.90), (37.45, 64.40), (37.45, 67.25), (37.15, 67.55),
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
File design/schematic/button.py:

"""Blocks onoff + ui: LTC2954-1 push-button controller, Q_EN inverter, Q_PWR high-side switch, KILL inverter,
POWER / RESET / MASKROM buttons and the three LEDs.

Sources: power.md §6.1 (circuit), §6.4a (LTC2954-1 + Q_EN, D-51), §6.5 (TP8a/a'/b/c); D-19 (PB_INT_N 4.7k),
D-20 (PWR_KILL 100k pull-down), D-41 (gate network); [LF] "Power Reset" (Key1 + R22 100R on NPOR) and
"System RECOVERY Key" (R21 10K to VCC_1V8, C44 1nF, R23 100R, Key2); D-09/D-21/D-69 (LEDs).
"""
from lib import part, two

GND = "GND"


def onoff():
    part("U_ONOFF", "LTC2954", {"VIN": "VBUS_5V", "PB": "PB_IN", "ONT": None,       # ONT open: tDB,ON 26-41 ms
                                "GND": GND, "INT": "PB_INT_N", "EN": "ONOFF_EN", "PDT": "ONOFF_PDT",
                                "KILL": "PWR_KILL_N"})
    two("C_ONOFF_VIN", "C", "VBUS_5V", GND, place_near="U_ONOFF pin 1")
    two("C_PDT", "C", "ONOFF_PDT", GND)        # 2.2 uF X5R (D-117 c: hard-off >= 8 s worst case; value from bom.csv)
    # POWER button -> 0R link -> PB (the [LTC] p.12 RC option is not fitted, power.md §6.1)
    part("SW_PWR", "TACT", {"1": "PWR_BTN_N", "2": "PWR_BTN_N", "3": GND, "4": GND})
    two("R_PB", "R", "PWR_BTN_N", "PB_IN")
    # EN (-1: active-high open drain) -> Q_EN inverter -> EN_N = EN-bar-equivalent node (TP8a)
    two("R_ENPU", "R", "VBUS_5V", "ONOFF_EN")
    part("Q_EN", "MOS", {"G": "ONOFF_EN", "S": GND, "D": "EN_N"})
    two("R_G", "R", "EN_N", "QPWR_G")
    # Q_PWR AO3401A: S = VBUS_5V, D = VCC5V0_SYS; gate network R_GS/C_GS (G-S), C_GD (G-D) per D-41
    part("Q_PWR", "MOS", {"G": "QPWR_G", "S": "VBUS_5V", "D": "VCC5V0_SYS"})
    two("R_GS", "R", "QPWR_G", "VBUS_5V")
    two("C_GS", "C", "QPWR_G", "VBUS_5V")
    two("C_GD", "C", "QPWR_G", "VCC5V0_SYS")
    two("R_BL5", "R", "VCC5V0_SYS", GND)
    # interrupt to SoC pin 60 (D-19) and kill path from SoC pin 63 (D-03/D-20)
    two("R_INTPU", "R", "VCC_3V3", "PB_INT_N")
    two("R_KU", "R", "VCC_3V3", "PWR_KILL_N")
    part("Q_KILL", "MOS", {"G": "PWR_KILL", "S": GND, "D": "PWR_KILL_N"})
    two("R_KILLPD", "R", "PWR_KILL", GND)


def ui():
    # RESET: NPOR -> R22 100R -> Key1 -> GND ([LF] "Power Reset"; ED1 TVS not fitted on [LF] and not placed here)
    two("R22", "R", "NPOR", "NPOR_KEY")
    part("SW_RESET", "TACT", {"1": "NPOR_KEY", "2": "NPOR_KEY", "3": GND, "4": GND})
    # MASKROM/RECOVERY: RECOVERY -> 100R -> Key2 -> GND ([LF] R23 100R; ED2 not fitted)
    two("R_RECOV", "R", "RECOVERY", "RECOVERY_KEY")
    part("SW_RECOV", "TACT", {"1": "RECOVERY_KEY", "2": "RECOVERY_KEY", "3": GND, "4": GND})
    # LEDs (KT-0603R red, 1k series)
    two("R_LED_PWR", "R", "VCC_3V3", "LED_PWR_A")
    part("LED_PWR", "LED", {"A": "LED_PWR_A", "K": GND})
    two("R_LED_STAT", "R", "VCC_3V3", "LED_STAT_A")                 # active-LOW on pin 62 (GPIO0_A3_u)
    part("LED_STAT", "LED", {"A": "LED_STAT_A", "K": "LED_STATUS"})
    two("R_LED_ETH", "R", "LED_ETH", "LED_ETH_A")                   # active-HIGH on pin 74 (GPIO1_A2_d)
    part("LED_ETH", "LED", {"A": "LED_ETH_A", "K": GND})

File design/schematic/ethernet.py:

"""Block eth: RJ45 with magnetics on the SoC's embedded 10/100 PHY.

Copy of [LF] "Ethernet" (J2): ETH_T_P/N, ETH_R_P/N through 0R R46-R49 to jack pins 1 TD+, 2 TD-, 3 RD+, 6 RD-;
centre taps 4 and 5 each 10 nF (103) to GND (C66/C67); pin 7 NC; pin 8 chassis -> ground ([LF] C68 '0R/1nF/100V';
Hanrun HR911105A datasheet p.1 note "Connect CHS GND to PCB Ground" -> direct GND here); jack shield to GND.
ETH_EXTR 6.04k is in soc.py. The jack's two LEDs (9/10 green, 11/12 yellow) are not used: the activity LED is the
discrete LED_ETH on pin 74 (D-21), so pins 9-12 are NC (D-72).
"""
from lib import part, two

GND = "GND"


def ethernet():
    two("R_ETH_TXP", "R", "ETH_TXP", "ETH_TXP_J")
    two("R_ETH_TXN", "R", "ETH_TXN", "ETH_TXN_J")
    two("R_ETH_RXP", "R", "ETH_RXP", "ETH_RXP_J")
    two("R_ETH_RXN", "R", "ETH_RXN", "ETH_RXN_J")
    part("J_RJ45", "RJ45", {"1": "ETH_TXP_J", "2": "ETH_TXN_J", "3": "ETH_RXP_J", "6": "ETH_RXN_J",
                            "4": "ETH_TCT", "5": "ETH_RCT", "7": None, "8": GND,
                            "9": None, "10": None, "11": None, "12": None, "SH": GND})
    two("C_CT_TX", "C", "ETH_TCT", GND, place_near="J_RJ45 pin 4")
    two("C_CT_RX", "C", "ETH_RCT", GND, place_near="J_RJ45 pin 5")
